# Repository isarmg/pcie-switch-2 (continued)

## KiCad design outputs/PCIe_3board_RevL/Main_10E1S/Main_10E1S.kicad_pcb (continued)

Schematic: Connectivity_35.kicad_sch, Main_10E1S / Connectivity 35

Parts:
U502: Intel Core Ultra 7 268V / BGA2833; Intel_Core_Ultra_200V_BGA2833_27p5x27_ExactXY_DraftLands
U601: 9ZXL0851EKILFT / CPU common clock 100MHz; REF_9ZXL0851EKILFT_KU1
U602: 9ZXL0851EKILFT / CPU common clock 100MHz; REF_9ZXL0851EKILFT_KU3
U603: 9FGV0241AKLF / DNP ALTERNATE CLOCK; REF_9FGV0241AKLF_KU2; not fitted
U604: 9DML0451AKILF / DNP ALTERNATE CLOCK; REF_9DML0451AKILF_KU5; not fitted
U605: TPS3808G09DBVR / SUPPORT NETWORK PENDING; REF_TPS3808G09DBVR_FU1
U606: W25Q32JWSSIQ_C2980995 / SUPPORT NETWORK PENDING; REF_W25Q32JWSSIQ_FU2
U607: TCA9548ARGER / SUPPORT NETWORK PENDING; REF_TCA9548ARGER_SU1
U701: W25Q256JWPIQ / 1.8V 32MiB BIOS; WSON-8-1EP_6x5mm_P1.27mm_EP3.4x4.3mm
U702: TPS7A0215PDBVR / RTC 1.5V; SOT-23-5

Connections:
/CLKBUF1_VDDA: U601.44 (VDDA); also elsewhere on the board
/CLKBUF2_VDDA: U602.44 (VDDA); also elsewhere on the board
/CPU_CLKBUF1_IN_N: U601.5 (DIF_IN#); also elsewhere on the board
/CPU_CLKBUF1_IN_P: U601.4 (DIF_IN); also elsewhere on the board
/CPU_CLKBUF2_IN_N: U602.5 (DIF_IN#); also elsewhere on the board
/CPU_CLKBUF2_IN_P: U602.4 (DIF_IN); also elsewhere on the board
/CPU_EPD_ON_LOOP_1V25: U502.Y27 (EPD_ON_IN); also elsewhere on the board
/CPU_PERST_1V8_N: U605.3 (MR); also elsewhere on the board
/CPU_SPI_CLK_FLASH: U701.6 (CLK); also elsewhere on the board
/CPU_SPI_CLK_PAD: U502.W13 (SPI0_CLK); also elsewhere on the board
/CPU_SPI_CS0_N: U701.1 (CS#); also elsewhere on the board
/CPU_SPI_IO0: U701.5 (IO0); also elsewhere on the board
/CPU_SPI_IO1: U701.2 (IO1); also elsewhere on the board
/CPU_SPI_IO2: U502.W17 (SPI0_IO2), U701.3 (IO2); also elsewhere on the board
/CPU_SPI_IO3: U502.U13 (SPI0_IO3), U701.7 (IO3); also elsewhere on the board
/CPU_USB2_RCOMP: U502.W1 (USB2_RCOMP); also elsewhere on the board
/CPU_VCCGT: U502.R70 (VCCGT), U502.R72 (VCCGT), U502.R74 (VCCGT), U502.R76 (VCCGT), U502.R78 (VCCGT), U502.R80 (VCCGT), U502.R82 (VCCGT), U502.R84 (VCCGT), U502.R86 (VCCGT), U502.R89 (VCCGT), U502.R92 (VCCGT), U502.T63 (VCCGT), U502.T65 (VCCGT), U502.T69 (VCCGT), U502.T71 (VCCGT), U502.T73 (VCCGT), U502.T77 (VCCGT), U502.T79 (VCCGT), U502.T81 (VCCGT), U502.T88 (VCCGT), U502.T90 (VCCGT), U502.T93 (VCCGT), U502.U89 (VCCGT), U502.V85 (VCCGT), U502.V88 (VCCGT), U502.V90 (VCCGT), U502.V93 (VCCGT), U502.W31 (VCCGT), U502.W34 (VCCGT), U502.W37 (VCCGT), U502.W40 (VCCGT), U502.W43 (VCCGT), U502.W46 (VCCGT), U502.W49 (VCCGT), U502.W51 (VCCGT), U502.W54 (VCCGT), U502.W57 (VCCGT), U502.W60 (VCCGT), U502.W63 (VCCGT), U502.W66 (VCCGT), U502.W69 (VCCGT), U502.W72 (VCCGT), U502.W75 (VCCGT), U502.W77 (VCCGT), U502.W80 (VCCGT), U502.W83 (VCCGT), U502.W86 (VCCGT), U502.W89 (VCCGT), U502.W92 (VCCGT), U502.Y30 (VCCGT), U502.Y33 (VCCGT), U502.Y36 (VCCGT), U502.Y38 (VCCGT), U502.Y41 (VCCGT), U502.Y44 (VCCGT), U502.Y47 (VCCGT), U502.Y50 (VCCGT), U502.Y53 (VCCGT), U502.Y56 (VCCGT), U502.Y59 (VCCGT), U502.Y62 (VCCGT), U502.Y64 (VCCGT), U502.Y67 (VCCGT), U502.Y70 (VCCGT), U502.Y73 (VCCGT), U502.Y76 (VCCGT), U502.Y79 (VCCGT), U502.Y82 (VCCGT), U502.Y85 (VCCGT), U502.Y88 (VCCGT), U502.Y90 (VCCGT), U502.Y93 (VCCGT); also elsewhere on the board
/CPU_VCCPRIM_1P8: U701.8 (VCC); also elsewhere on the board
/CPU_VCCRTC: U702.5 (OUT); also elsewhere on the board
/GND: U502.T2 (VSS), U502.T9 (VSS), U502.T17 (VSS), U502.T19 (VSS), U502.T21 (VSS), U502.T23 (VSS), U502.T27 (VSS), U502.T29 (VSS), U502.T31 (VSS), U502.T35 (VSS), U502.T37 (VSS), U502.T39 (VSS), U502.T41 (VSS), U502.T43 (VSS), U502.T45 (VSS), U502.T47 (VSS), U502.T49 (VSS), U502.T51 (VSS), U502.T53 (VSS), U502.T55 (VSS), U502.T57 (VSS), U502.T59 (VSS), U502.T61 (VSS), U502.T67 (VSS), U502.T75 (VSS), U502.T83 (VSS), U502.U3 (VSS), U502.U15 (VSS), U502.U86 (VSS), U502.U92 (VSS), U502.V4 (VSS), U502.W3 (VSS), U502.W11 (VSS), U502.W20 (VSS), U502.W26 (VSS), U502.W28 (VSS), U502.Y15 (VSS), U502.Y18 (VSS), U502.Y21 (VSS), U502.Y24 (VSS), U601.2 (GNDR), U601.11 (VOE0#), U601.18 (VOE1#), U601.23 (VOE2#), U601.24 (VOE3#), U601.30 (VOE4#), U601.31 (VOE5#), U601.37 (VOE6#), U601.41 (VOE7#), U601.49 (GND), U602.2 (GNDR), U602.11 (VOE0#), U602.18 (VOE1#), U602.23 (VOE2#), U602.24 (VOE3#), U602.30 (VOE4#), U602.31 (VOE5#), U602.37 (VOE6#), U602.41 (VOE7#), U602.49 (GND), U603.5 (GNDREF), U603.6 (GNDDIG), U603.10 (GND), U603.12 (vOE0#), U603.15 (GNDA), U603.21 (GND), U603.24 (GNDXTAL), U603.25 (EP), U604.7 (GNDR), U604.9 (^OE0#), U604.12 (^OE1#), U604.15 (GND), U604.19 (^OE2#), U604.22 (^OE3#), U604.24 (GNDR), U604.25 (TH), U605.2 (GND), U606.4 (GND), U607.9 (GND), U607.25 (EP), U701.4 (GND), U701.9 (EP), U702.2 (GND); also elsewhere on the board
/M1_CLK_N: U602.26 (DIF3#); also elsewhere on the board
/M1_CLK_P: U602.25 (DIF3); also elsewhere on the board
/M2_CLK_N: U602.29 (DIF4#); also elsewhere on the board
/M2_CLK_P: U602.28 (DIF4); also elsewhere on the board
/M3_CLK_N: U602.33 (DIF5#); also elsewhere on the board
/M3_CLK_P: U602.32 (DIF5); also elsewhere on the board
/M4_CLK_N: U602.36 (DIF6#); also elsewhere on the board
/M4_CLK_P: U602.35 (DIF6); also elsewhere on the board
/M5_CLK_N: U602.40 (DIF7#); also elsewhere on the board
/M5_CLK_P: U602.39 (DIF7); also elsewhere on the board
/P3V3_AUX: U601.1 (^CKPWRGD_PD#), U601.3 (VDDR), U601.10 (VDD), U601.15 (VDD), U601.19 (VDD), U601.27 (VDD), U601.34 (VDD), U601.38 (VDD), U601.42 (VDD), U601.47 (^100M_133M#), U601.48 (^HIBW_BYPM_LOBW#), U602.1 (^CKPWRGD_PD#), U602.3 (VDDR), U602.10 (VDD), U602.15 (VDD), U602.19 (VDD), U602.27 (VDD), U602.34 (VDD), U602.38 (VDD), U602.42 (VDD), U602.47 (^100M_133M#), U602.48 (^HIBW_BYPM_LOBW#), U605.6 (VDD), U607.21 (VCC), U702.1 (IN), U702.3 (EN); also elsewhere on the board
/PEX_0V9: U605.5 (SENSE); also elsewhere on the board
/PEX_1V8: U606.8 (VCC); also elsewhere on the board
/PEX_RESET_CT: U605.4 (CT); also elsewhere on the board
/PEX_SPI_CLK: U606.6 (CLK); also elsewhere on the board
/PEX_SPI_CS_N: U606.1 (CS#); also elsewhere on the board
/PEX_SPI_IO0: U606.5 (IO0); also elsewhere on the board
/PEX_SPI_IO1: U606.2 (IO1); also elsewhere on the board
/PEX_SPI_IO2: U606.3 (IO2); also elsewhere on the board
/PEX_SPI_IO3: U606.7 (IO3); also elsewhere on the board
/PEX_SYS_REFCLK_N: U601.14 (DIF0#); also elsewhere on the board
/PEX_SYS_REFCLK_P: U601.13 (DIF0); also elsewhere on the board
/PEX_SYS_RESET_N: U605.1 (RESET); also elsewhere on the board
/REF_KA_DIF0N: U603.14 (DIF0#)
/REF_KA_DIF0P: U603.13 (DIF0)
/REF_KA_OE1: U603.19 (vOE1#)
/REF_KA_PD#: U603.22 (^CKPWRGD_PD#)
/REF_KA_SSEN: U603.23 (vSS_EN_tri)
/REF_KA_VDD: U603.3 (VDDXTAL1.8), U603.7 (VDDDIG1.8), U603.11 (VDD1.8), U603.20 (VDD1.8)
/REF_KA_VDDA: U603.16 (VDDA1.8)
/REF_KA_X1: U603.1 (X1_25)
/REF_KA_X2: U603.2 (X2)
/REF_KB_DIF0N: U604.11 (DIF0#)
/REF_KB_DIF0P: U604.10 (DIF0)
/REF_KB_DIF1N: U604.14 (DIF1#)
/REF_KB_DIF1P: U604.13 (DIF1)
/REF_KB_DIF2N: U604.18 (DIF2#)
/REF_KB_DIF2P: U604.17 (DIF2)
/REF_KB_DIF3N: U604.21 (DIF3#)
/REF_KB_DIF3P: U604.20 (DIF3)
/REF_KB_MODE: U604.8 (vSW_MODE)
/REF_KB_SELAB: U604.23 (^SEL_A_B#)
/REF_KB_VDD: U604.16 (VDD3.3)
/REF_KB_VDDA: U604.3 (VDDR3.3A)
/REF_KB_VDDB: U604.4 (VDDR3.3B)
/REF_PERST_BUFF#: U607.24 (RESET#)
/REF_PE_REFCLKN: U604.2 (DIF_INA#)
/REF_PE_REFCLKP: U604.1 (DIF_INA)
/REF_SLIMA0_CLK: U607.17 (SC7)
/REF_SLIMA0_DAT: U607.16 (SD7)
/REF_SLIMA1_CLK: U607.15 (SC6)
/REF_SLIMA1_DAT: U607.14 (SD6)
/REF_SLIMA2_CLK: U607.13 (SC5)
/REF_SLIMA2_DAT: U607.12 (SD5)
/REF_SLIMA3_CLK: U607.11 (SC4)
/REF_SLIMA3_DAT: U607.10 (SD4)
/REF_SLIMB0_CLK: U607.8 (SC3)
/REF_SLIMB0_DAT: U607.7 (SD3)
/REF_SLIMB1_CLK: U607.6 (SC2)
/REF_SLIMB1_DAT: U607.5 (SD2)
/REF_SLIMB2_CLK: U607.4 (SC1)
/REF_SLIMB2_DAT: U607.3 (SD1)
/REF_SLIMB3_CLK: U607.2 (SC0)
/REF_SLIMB3_DAT: U607.1 (SD0)
/REF_SMB_A_A0: U607.22 (A0)
/REF_SMB_A_A1: U607.23 (A1)
/REF_SMB_A_A2: U607.18 (A2)
/REF_SMB_A_SCL: U607.19 (SCL)
/REF_SMB_A_SDA: U607.20 (SDA)
/REF_SRNS_REFCLKN: U604.6 (DIF_INB#)
/REF_SRNS_REFCLKP: U604.5 (DIF_INB)
/S01_REFCLK0_N: U601.17 (DIF1#); also elsewhere on the board
/S01_REFCLK0_P: U601.16 (DIF1); also elsewhere on the board
/S02_REFCLK0_N: U601.22 (DIF2#); also elsewhere on the board
/S02_REFCLK0_P: U601.21 (DIF2); also elsewhere on the board
/S03_REFCLK0_N: U601.26 (DIF3#); also elsewhere on the board
/S03_REFCLK0_P: U601.25 (DIF3); also elsewhere on the board
/S04_REFCLK0_N: U601.29 (DIF4#); also elsewhere on the board
/S04_REFCLK0_P: U601.28 (DIF4); also elsewhere on the board
/S05_REFCLK0_N: U601.33 (DIF5#); also elsewhere on the board
/S05_REFCLK0_P: U601.32 (DIF5); also elsewhere on the board
/S06_REFCLK0_N: U601.36 (DIF6#); also elsewhere on the board
/S06_REFCLK0_P: U601.35 (DIF6); also elsewhere on the board
/S07_REFCLK0_N: U601.40 (DIF7#); also elsewhere on the board
/S07_REFCLK0_P: U601.39 (DIF7); also elsewhere on the board
/S08_REFCLK0_N: U602.14 (DIF0#); also elsewhere on the board
/S08_REFCLK0_P: U602.13 (DIF0); also elsewhere on the board
/S09_REFCLK0_N: U602.17 (DIF1#); also elsewhere on the board
/S09_REFCLK0_P: U602.16 (DIF1); also elsewhere on the board
/S10_REFCLK0_N: U602.22 (DIF2#); also elsewhere on the board
/S10_REFCLK0_P: U602.21 (DIF2); also elsewhere on the board

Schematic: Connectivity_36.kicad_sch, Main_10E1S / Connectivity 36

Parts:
Y701: 38.4MHz crystal / load and ESR selection pending; Crystal_SMD_3225-4Pin_3.2x2.5mm
Y702: 32.768kHz crystal / load and ESR selection pending; Crystal_SMD_2012-2Pin_2.0x1.2mm

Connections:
/CPU_RTCX1: Y702.1; also elsewhere on the board
/CPU_RTCX2: Y702.2; also elsewhere on the board
/CPU_XTAL_IN: Y701.1; also elsewhere on the board
/CPU_XTAL_OUT: Y701.3; also elsewhere on the board
/GND: Y701.2, Y701.4; also elsewhere on the board

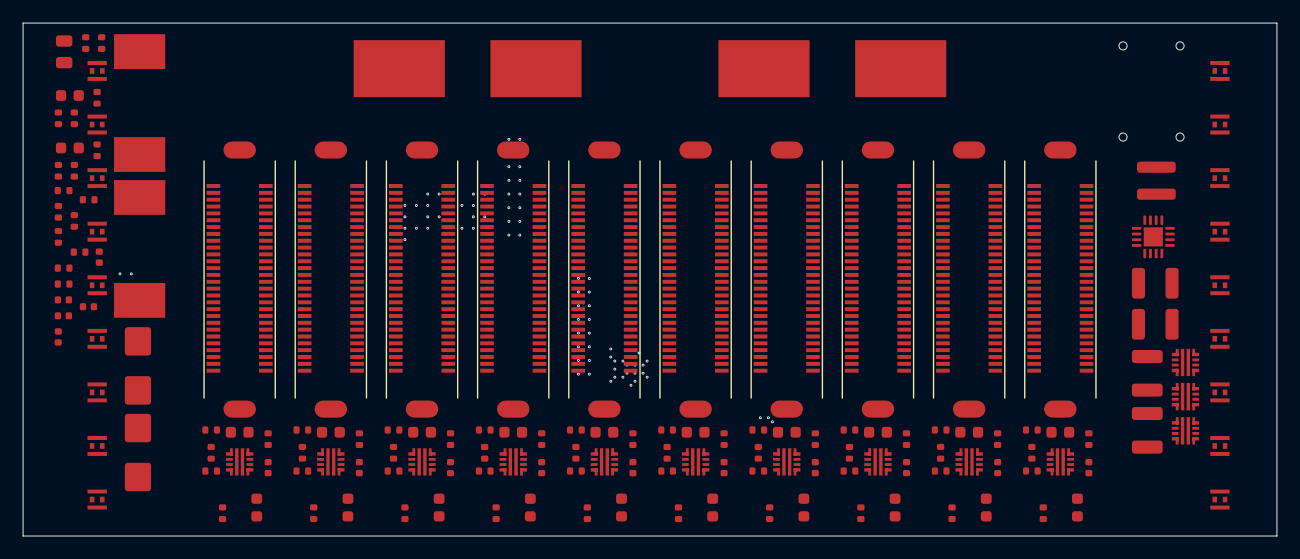
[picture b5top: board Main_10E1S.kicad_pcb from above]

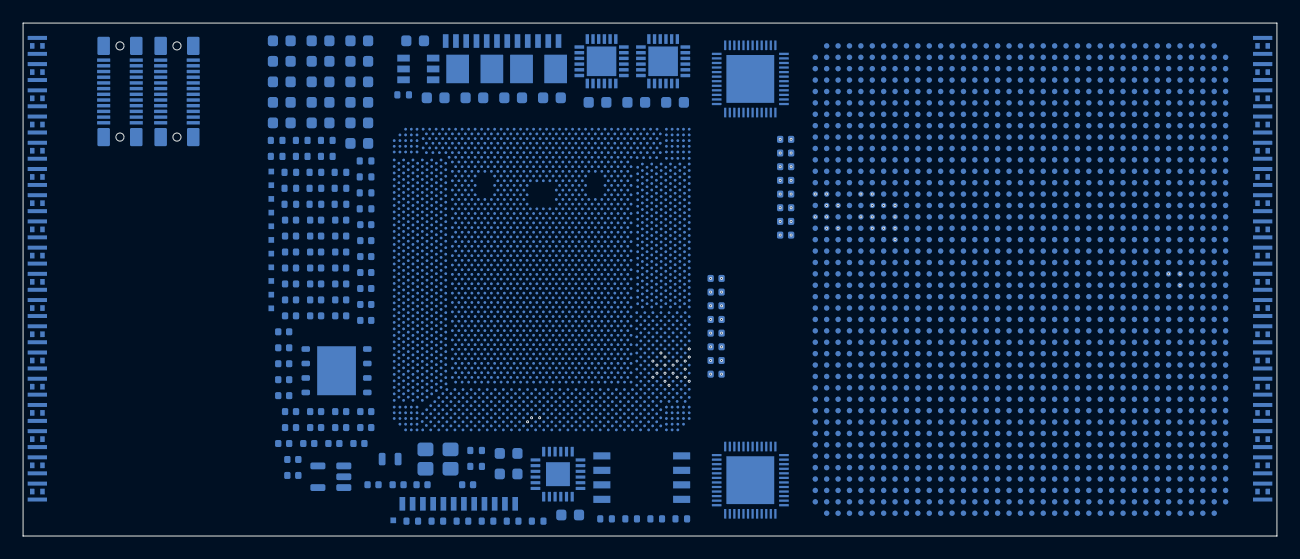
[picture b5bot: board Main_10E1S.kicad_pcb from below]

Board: 32 copper layers, 110.0 x 45.0 mm, 351 parts (194 on the bottom side), 492 nets.

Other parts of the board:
U501: Intel_JHL9580_MECH_13x13_UNVERIFIED

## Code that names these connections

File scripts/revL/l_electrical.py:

"""Mandatory external biases and Intel's required EPD loop from pp116-121."""
from pathlib import Path
import sys,json
sys.stdout.reconfigure(encoding='utf-8')
R=Path('C:/Users/micro/Desktop/方案/pcie switch 2')
sys.path.insert(0,str(R/'scripts/revJ'))
import i_common as c
from i_common import *
O=R/'outputs/PCIe_3board_RevL';folder=O/'Main_10E1S';bp=folder/'Main_10E1S.kicad_pcb';b=p.LoadBoard(str(bp))
a=object.__new__(Board);a.b=b;a.folder=folder;a.lib=folder/'Local.pretty';a.models=folder/'models';a.cs=[];a.newrefs=[];a.nets={n.GetNetname():n for n in b.GetNetInfo().NetsByNetcode().values()}
meta={x['ref']:x for x in json.loads((folder/'COMPONENTS.json').read_text(encoding='utf-8'))}
renames={'/CPU_EPD_ON_IN':'/CPU_EPD_ON_LOOP_1V25','/CPU_EPD_ON_OUT':'/CPU_EPD_ON_LOOP_1V25','/CPU_PLT_PWROK_1V8':'/CPU_PLT_PWROK','/CPU_RSMRST_1V8_N':'/CPU_RSMRST_N'}
for ff in b.GetFootprints():
    for pp in ff.Pads():
        if pp.GetNetname() in renames:pp.SetNet(a.net(renames[pp.GetNetname()]))
cpu=b.FindFootprintByReference('U502')
gpio={'GPP_V00':'/CPU_BATLOW_N','GPP_V01':'/CPU_ACPRESENT','GPP_E21':'/CPU_PMCALERT_N','GPP_V12':'/CPU_WAKE_N'}
for pp in cpu.Pads():
    primary=meta['U502']['pin_names'][pp.GetNumber()].split('/')[0]
    if primary in gpio:pp.SetNet(a.net(gpio[primary]))
for i,(nn,pull) in enumerate([('/CPU_BATLOW_N','/CPU_VCCPRIM_1P8'),('/CPU_ACPRESENT','/CPU_VCCPRIM_1P8'),('/CPU_PMCALERT_N','/CPU_VCCPRIM_1P8'),('/CPU_WAKE_N','/CPU_VCCPRIM_1P8'),('/CPU_RSMRST_N','/GND'),('/CPU_PLT_PWROK','/GND'),('/CPU_SYS_PWROK_1V8','/GND')]):
    ref=f'R{740+i}'
    if not b.FindFootprintByReference(ref):a.place(ref,'10k / Intel required external bias','R_0402_1005Metric',0,0,{'1':nn,'2':pull},'B',0,.4)
for e in a.cs:meta[e['ref']]=e
# KiCad uses the open_collector enum for both open-collector and open-drain
# pins. "open_drain" is not a valid symbol-file token and prevents the CPU
# cached symbol, and neighbouring cached symbols, from loading.
meta['U502']['pin_types']={k:('open_collector' if v=='open_drain' else v) for k,v in meta['U502']['pin_types'].items()}
for ff in b.GetFootprints():
    e=meta[ff.GetReference()];e.update(pinmap={pp.GetNumber():pp.GetNetname() for pp in ff.Pads() if pp.GetNumber()})
    for old,new in renames.items():
        if old in ff.GetValue():ff.SetValue(ff.GetValue().replace(old,new));e['value']=ff.GetValue()
(folder/'COMPONENTS.json').write_text(json.dumps(list(meta.values()),ensure_ascii=False,indent=2),encoding='utf-8')
p.SaveBoard(str(bp),b)
print('Added required external biases and joined EPD_ON_IN/OUT; unverified control voltages left unnamed.',flush=True)

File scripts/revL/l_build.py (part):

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 'EPD_ON_IN':'/CPU_EPD_ON_IN','EPD_ON_OUT':'/CPU_EPD_ON_OUT','VDD2PWRGOOD_IN':'/CPU_VDD2_PWRGOOD_LOOP','VDD2PWRGOOD_OUT':'/CPU_VDD2_PWRGOOD_LOOP',
 'SPI0_CLK':'/CPU_SPI_CLK_PAD','SPI0_CS0#':'/CPU_SPI_CS0_N','SPI0_MISO':'/CPU_SPI_IO1','SPI0_MOSI':'/CPU_SPI_IO0','SPI0_IO2':'/CPU_SPI_IO2','SPI0_IO3':'/CPU_SPI_IO3',
 'CLK_S_RCOMP':'/CPU_CLK_RCOMP','PCIE4_RCOMP':'/CPU_PCIE4_RCOMP','PCIE5_RCOMP':'/CPU_PCIE5_RCOMP','USB2_RCOMP':'/CPU_USB2_RCOMP','USB32_RCOMP':'/CPU_USB32_RCOMP'})
gpio_map={'GPP_B13':'/CPU_PERST_1V8_N','GPP_C09':'/CPU_CLKREQ0_N','GPP_C10':'/CPU_CLKREQ1_N','GPP_C11':'/CPU_CLKREQ2_N',
 'GPP_V03':'/CPU_PWRBTN_1V8_N','GPP_V04':'/CPU_SLP_S3_1V8_N','GPP_V05':'/CPU_SLP_S4_1V8_N','GPP_V09':'/CPU_SLP_S5_1V8_N','GPP_V16':'/CPU_VCCST_EN_1V8'}
rail_names=sorted({q['signal'] for q in cpu['pins'] if q['interface']=='Power' and q['signal']!='VSS' and not any(k in q['signal'] for k in ['SENSE','EDGECAP','FLTR','PWRGOOD']) and not q['signal'].startswith('VID')})
pinmap={};types={}
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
